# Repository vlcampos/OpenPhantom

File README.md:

# OpenPhantom
OpenPhantom is an open-source hardware project of a replacement main board for the Gradiente Phantom System model PH-8. The most famous NES clone made in Brazil during the 1980s and early 1990s.
The board was made as a hobby project based on a real board, internet schematics and a lot of reverse engineering.

Some modifications were made to make it easier to reproduce in Brazil and make it a little bit cheaper.
You can check the development progress on my twitter: @vagnerlc.
You are also invited to show any enhancements, modifications and make questions if needed.

You are free to use it in anyway you want: reproduce, sell, mod, etc.

I'm just a hobbyst trying to repair my old consoles and keep the very interesting history of this console alive.

The software used for the schematics was the Kicad 6.0.

Enjoy!

OpenPhantom é um projeto open-source para uma placa de reposição para o Phantom System PH-8 da Gradiente, o mais famoso dos clones de Nintendinho feitos no Brasil nas décadas de 80 e 90.
Essa placa surgiu como um hobby que envolveu uma placa com problemas, esquemas de internet e um bocado de engenharia revera.

Algumas modificações foram feitas para facilitar a reprodução da placa no Brasil.
Se quiserem acompanhar como foi o desenvolvimento é só ver meu twitter @vagnerlc.
Mandem as modificações, melhorias e projetos pessoais lá também e em caso de dúvidas é só me chamar por lá.

Por ser open source vocês podem usar o projeto do jeito que quiserem: venda, reprodução, modificação, etc...

Eu sou só um hobista tentando consertar minhas velharias e manter a história desse console viva.

Para o desenvolvimento foi utilizado o Kicad 6.0.

Divirtam-se!

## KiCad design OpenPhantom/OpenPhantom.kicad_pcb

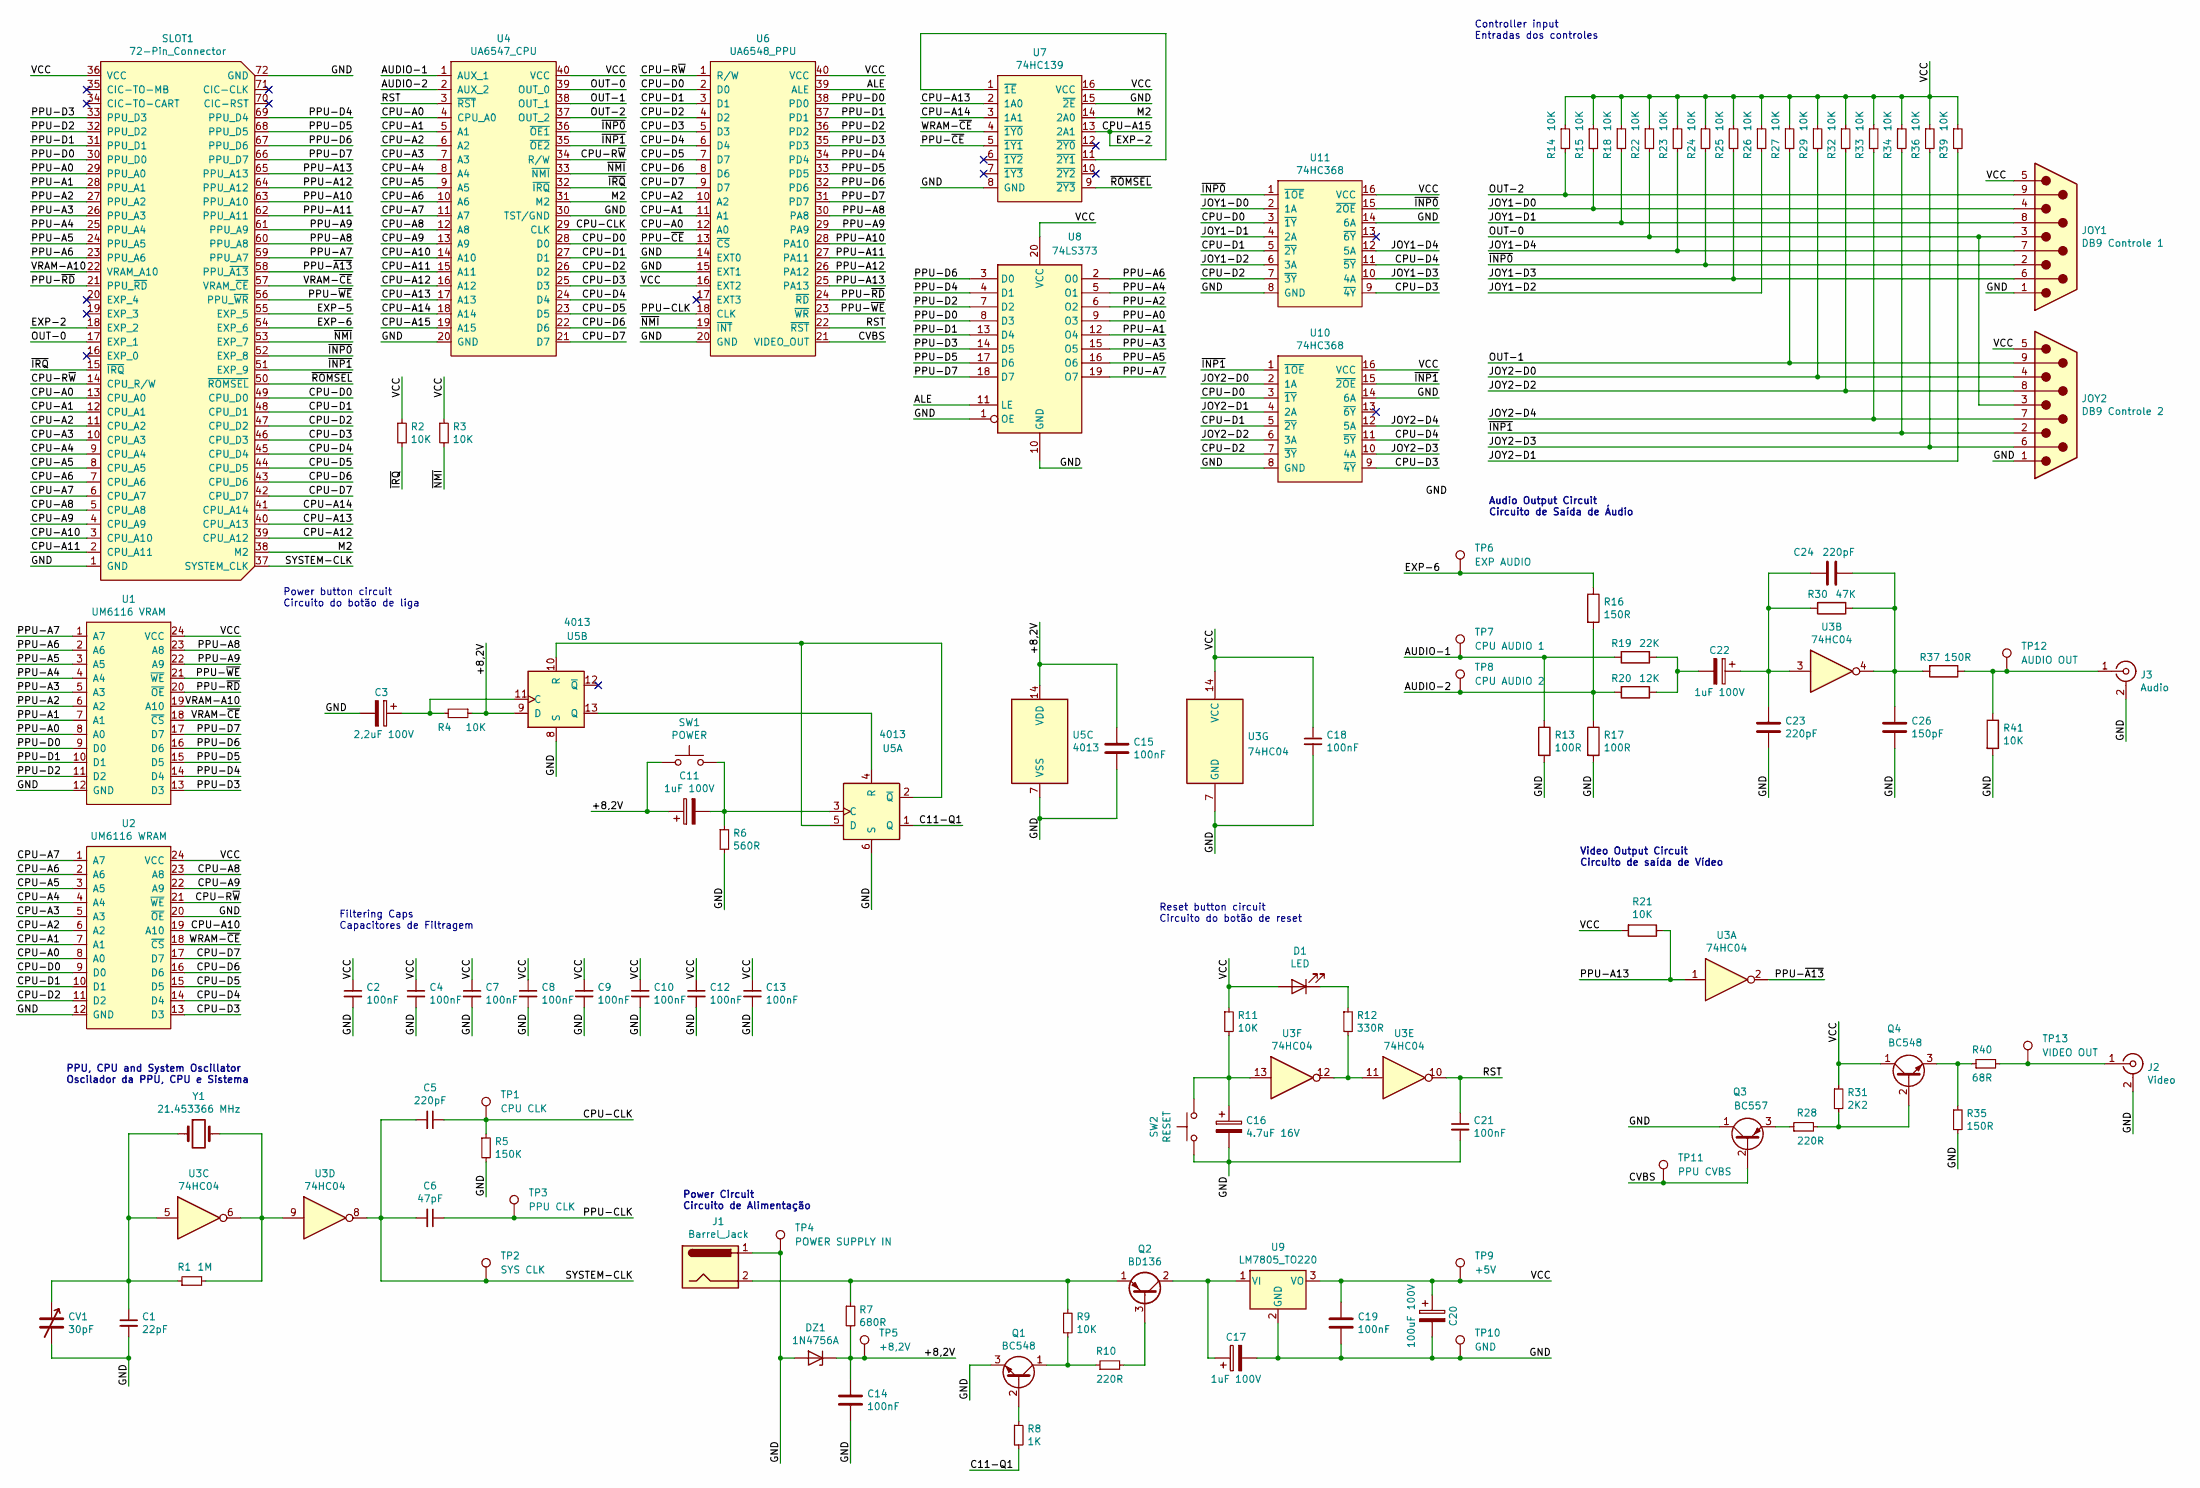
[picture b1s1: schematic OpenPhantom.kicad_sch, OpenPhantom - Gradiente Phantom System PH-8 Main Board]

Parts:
C1: 22pF; C_Disc_D4.7mm_W2.5mm_P5.00mm
C2, C4, C7, C8, C9, C10, C12, C13, C14, C15, C18, C19, C21: 100nF; C_Disc_D4.7mm_W2.5mm_P5.00mm
C3: 2,2uF 100V; CP_Radial_D5.0mm_P2.50mm
C5, C23, C24: 220pF; C_Disc_D4.7mm_W2.5mm_P5.00mm
C6: 47pF; C_Disc_D4.7mm_W2.5mm_P5.00mm
C11, C17, C22: 1uF 100V; CP_Radial_D5.0mm_P2.50mm
C16: 4.7uF 16V; CP_Radial_D5.0mm_P2.50mm
C20: 100uF 100V; CP_Radial_D5.0mm_P2.50mm
C26: 150pF; C_Disc_D4.7mm_W2.5mm_P5.00mm
CV1: 30pF; TrimmerCap-THT
D1: LED; LED_D5.0mm
DZ1: 1N4756A; D_DO-41_SOD81_P10.16mm_Horizontal
J1: Barrel_Jack; BarrelJack_Horizontal
J2: Video; rca_yellow
J3: Audio; rca_white
JOY1: DB9 Controle 1; DSUB-9_Male_Horizontal_P2.77x2.84mm_EdgePinOffset7.70mm_Hou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
JOY2: DB9 Controle 2; DSUB-9_Male_Horizontal_P2.77x2.84mm_EdgePinOffset7.70mm_Hou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
Q1, Q4: BC548; TO-92_HandSolder
Q2: BD136; TO-126-3_Vertical
Q3: BC557; TO-92_HandSolder
R1: 1M; R_Axial_DIN0207_L6.3mm_D2.5mm_P10.16mm_Horizontal
R2, R3, R4, R9, R11, R14, R15, R18, R21, R22, R23, R24, R25, R26, R27, R29, R32, R33, R34, R36, R39, R41: 10K; R_Axial_DIN0207_L6.3mm_D2.5mm_P10.16mm_Horizontal
R5: 150K; R_Axial_DIN0207_L6.3mm_D2.5mm_P10.16mm_Horizontal
R6: 560R; R_Axial_DIN0207_L6.3mm_D2.5mm_P10.16mm_Horizontal
R7: 680R; R_Axial_DIN0207_L6.3mm_D2.5mm_P10.16mm_Horizontal
R8: 1K; R_Axial_DIN0207_L6.3mm_D2.5mm_P10.16mm_Horizontal
R10: 220R; R_Axial_DIN0204_L3.6mm_D1.6mm_P7.62mm_Horizontal
R12: 330R; R_Axial_DIN0207_L6.3mm_D2.5mm_P10.16mm_Horizontal
R13, R17: 100R; R_Axial_DIN0207_L6.3mm_D2.5mm_P10.16mm_Horizontal
R16, R35, R37: 150R; R_Axial_DIN0207_L6.3mm_D2.5mm_P10.16mm_Horizontal
R19: 22K; R_Axial_DIN0207_L6.3mm_D2.5mm_P10.16mm_Horizontal
R20: 12K; R_Axial_DIN0207_L6.3mm_D2.5mm_P10.16mm_Horizontal
R28: 220R; R_Axial_DIN0207_L6.3mm_D2.5mm_P10.16mm_Horizontal
R30: 47K; R_Axial_DIN0207_L6.3mm_D2.5mm_P10.16mm_Horizontal
R31: 2K2; R_Axial_DIN0207_L6.3mm_D2.5mm_P10.16mm_Horizontal
R40: 68R; R_Axial_DIN0207_L6.3mm_D2.5mm_P10.16mm_Horizontal
SLOT1: 72-Pin_Connector; Conector_NES_72pinos
SW1: POWER; SW_PUSH_6mm
SW2: RESET; SW_PUSH_6mm
TP1: CPU CLK; TestPoint_Pad_1.0x1.0mm
TP2: SYS CLK; TestPoint_Pad_1.0x1.0mm
TP3: PPU CLK; TestPoint_Pad_1.0x1.0mm
TP4: POWER SUPPLY IN; TestPoint_Pad_1.0x1.0mm
TP5: +8,2V; TestPoint_Pad_1.0x1.0mm
TP6: EXP AUDIO; TestPoint_Pad_1.0x1.0mm
TP7: CPU AUDIO 1; TestPoint_Pad_1.0x1.0mm
TP8: CPU AUDIO 2; TestPoint_Pad_1.0x1.0mm
TP9: +5V; TestPoint_Pad_1.0x1.0mm
TP10: GND; TestPoint_Pad_1.0x1.0mm
TP11: PPU CVBS; TestPoint_Pad_1.0x1.0mm
TP12: AUDIO OUT; TestPoint_Pad_1.0x1.0mm
TP13: VIDEO OUT; TestPoint_Pad_1.0x1.0mm
U1: UM6116 VRAM; DIP-24_W15.24mm
U2: UM6116 WRAM; DIP-24_W15.24mm
U3: 74HC04; DIP-14_W7.62mm
U4: UA6547_CPU; DIP-40_W15.24mm
U5: 4013; DIP-14_W7.62mm
U6: UA6548_PPU; DIP-40_W15.24mm
U7: 74HC139; DIP-16_W7.62mm
U8: 74LS373; DIP-20_W7.62mm
U9: LM7805_TO220; TO-220-3_Vertical
U10, U11: 74HC368; DIP-16_W7.62mm
Y1: 21.453366 MHz; Crystal_HC18-U_Vertical

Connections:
/+8,2V: C11.1, C14.1, C15.1, DZ1.1 (K), R4.1, R7.2, SW1.1, TP5.1, U5.9 (D), U5.14 (VDD)
/ALE: U6.39 (ALE), U8.11 (LE)
/AUDIO-1: R13.1, R19.2, TP7.1, U4.1 (AUX_1)
/AUDIO-2: R16.2, R17.1, R20.2, TP8.1, U4.2 (AUX_2)
/C11-Q1: R8.2, U5.1 (Q)
/CPU-A0: SLOT1.13 (CPU_A0), U2.8 (A0), U4.4 (CPU_A0), U6.12 (A0)
/CPU-A1: SLOT1.12 (CPU_A1), U2.7 (A1), U4.5 (A1), U6.11 (A1)
/CPU-A2: SLOT1.11 (CPU_A2), U2.6 (A2), U4.6 (A2), U6.10 (A2)
/CPU-A3: SLOT1.10 (CPU_A3), U2.5 (A3~), U4.7 (A3)
/CPU-A4: SLOT1.9 (CPU_A4), U2.4 (A4~), U4.8 (A4)
/CPU-A5: SLOT1.8 (CPU_A5), U2.3 (A5~), U4.9 (A5)
/CPU-A6: SLOT1.7 (CPU_A6), U2.2 (A6~), U4.10 (A6)
/CPU-A7: SLOT1.6 (CPU_A7), U2.1 (A7), U4.11 (A7)
/CPU-A8: SLOT1.5 (CPU_A8), U2.23 (A8), U4.12 (A8)
/CPU-A9: SLOT1.4 (CPU_A9), U2.22 (A9), U4.13 (A9)
/CPU-A10: SLOT1.3 (CPU_A10), U2.19 (A10), U4.14 (A10)
/CPU-A11: SLOT1.2 (CPU_A11), U4.15 (A11)
/CPU-A12: SLOT1.39 (CPU_A12), U4.16 (A12)
/CPU-A13: SLOT1.40 (CPU_A13), U4.17 (A13), U7.2 (1A0)
/CPU-A14: SLOT1.41 (CPU_A14), U4.18 (A14), U7.3 (1A1)
/CPU-A15: SLOT1.18 (EXP_2), U4.19 (A15), U7.13 (2A1)
/CPU-CLK: C5.1, R5.1, TP1.1, U4.29 (CLK)
/CPU-D0: SLOT1.49 (CPU_D0), U2.9 (D0), U4.28 (D0), U6.2 (D0), U10.3 (~1Y), U11.3 (~1Y)
/CPU-D1: SLOT1.48 (CPU_D1), U2.10 (D1), U4.27 (D1), U6.3 (D1), U10.5 (~2Y), U11.5 (~2Y)
/CPU-D2: SLOT1.47 (CPU_D2), U2.11 (D2), U4.26 (D2), U6.4 (D2), U10.7 (~3Y), U11.7 (~3Y)
/CPU-D3: SLOT1.46 (CPU_D3), U2.13 (D3), U4.25 (D3), U6.5 (D3), U10.9 (~4Y), U11.9 (~4Y)
/CPU-D4: SLOT1.45 (CPU_D4), U2.14 (D4), U4.24 (D4), U6.6 (D4), U10.11 (~5Y), U11.11 (~5Y)
/CPU-D5: SLOT1.44 (CPU_D5), U2.15 (D5), U4.23 (D5), U6.7 (D7)
/CPU-D6: SLOT1.43 (CPU_D6), U2.16 (D6), U4.22 (D6), U6.8 (D6)
/CPU-D7: SLOT1.42 (CPU_D7), U2.17 (D7), U4.21 (D7), U6.9 (D7)
/CPU-R~W: SLOT1.14 (CPU_R/W), U2.21 (~WE), U4.34 (R/W), U6.1 (R/W)
/CVBS: Q3.2 (B), TP11.1, U6.21 (VIDEO_OUT)
/EXP-5: SLOT1.55 (EXP_5)
/EXP-6: R16.1, SLOT1.54 (EXP_6), TP6.1
/GND: C1.2, C2.2, C3.2, C4.2, C7.2, C8.2, C9.2, C10.2, C12.2, C13.2, C14.2, C15.2, C16.2, C17.2, C18.2, C19.2, C20.2, C21.2, C23.2, C26.2, CV1.2, DZ1.2 (A), J1.1, J2.2 (Ext), J3.2 (Ext), JOY1.1, JOY2.1, Q1.3 (E), Q3.1 (C), R5.2, R6.2, R13.2, R17.2, R35.2, R41.2, SLOT1.1 (GND), SLOT1.72 (GND), SW2.1, TP4.1, TP10.1, U1.12 (GND~), U2.12 (GND~), U2.20 (~OE), U3.7 (GND), U4.20 (GND), U4.30 (TST/GND), U5.6 (S), U5.7 (VSS), U5.8 (S), U6.14 (EXT0), U6.15 (EXT1), U6.20 (GND), U7.8 (GND), U7.15 (~2E), U8.1 (OE), U8.10 (GND), U9.2 (GND), U10.8 (GND), U10.14 (6A), U11.8 (GND), U11.14 (6A)
/JOY1-D0: JOY1.4, R15.2, U11.2 (1A)
/JOY1-D1: JOY1.8, R18.2, U11.4 (2A)
/JOY1-D2: R26.2, U11.6 (3A)
/JOY1-D3: JOY1.6, R25.2, U11.10 (4A)
/JOY1-D4: JOY1.7, R23.2, U11.12 (5A)
/JOY2-D0: JOY2.4, R29.2, U10.2 (1A)
/JOY2-D1: R39.2, U10.4 (2A)
/JOY2-D2: JOY2.8, R32.2, U10.6 (3A)
/JOY2-D3: JOY2.6, R36.2, U10.10 (4A)
/JOY2-D4: JOY2.7, R33.2, U10.12 (5A)
/M2: SLOT1.38 (M2), U4.31 (M2), U7.14 (2A0)
/OUT-0: JOY1.3, JOY2.3, R22.2, SLOT1.17 (EXP_1), U4.39 (OUT_0)
/OUT-1: JOY2.9, R27.2, U4.38 (OUT_1)
/OUT-2: JOY1.9, R14.2, U4.37 (OUT_2)
/PPU-A0: SLOT1.29 (PPU_A0), U1.8 (A0), U8.9 (O3)
/PPU-A1: SLOT1.28 (PPU_A1), U1.7 (A1), U8.12 (O4)
/PPU-A2: SLOT1.27 (PPU_A2), U1.6 (A2), U8.6 (O2)
/PPU-A3: SLOT1.26 (PPU_A3), U1.5 (A3~), U8.15 (O5)
/PPU-A4: SLOT1.25 (PPU_A4), U1.4 (A4~), U8.5 (O1)
/PPU-A5: SLOT1.24 (PPU_A5), U1.3 (A5~), U8.16 (O6)
/PPU-A6: SLOT1.23 (PPU_A6), U1.2 (A6~), U8.2 (O0)
/PPU-A7: SLOT1.59 (PPU_A7), U1.1 (A7), U8.19 (O7)
/PPU-A8: SLOT1.60 (PPU_A8), U1.23 (A8), U6.30 (PA8)
/PPU-A9: SLOT1.61 (PPU_A9), U1.22 (A9), U6.29 (PA9)
/PPU-A10: SLOT1.63 (PPU_A10), U6.28 (PA10)
/PPU-A11: SLOT1.62 (PPU_A11), U6.27 (PA11)
/PPU-A12: SLOT1.64 (PPU_A12), U6.26 (PA12)
/PPU-A13: R21.1, SLOT1.65 (PPU_A13), U3.1, U6.25 (PA13)
/PPU-CLK: C6.1, TP3.1, U6.18 (CLK)
/PPU-D0: SLOT1.30 (PPU_D0), U1.9 (D0), U6.38 (PD0), U8.8 (D3)
/PPU-D1: SLOT1.31 (PPU_D1), U1.10 (D1), U6.37 (PD1), U8.13 (D4)
/PPU-D2: SLOT1.32 (PPU_D2), U1.11 (D2), U6.36 (PD2), U8.7 (D2)
/PPU-D3: SLOT1.33 (PPU_D3), U1.13 (D3), U6.35 (PD3), U8.14 (D5)
/PPU-D4: SLOT1.69 (PPU_D4), U1.14 (D4), U6.34 (PD4), U8.4 (D1)
/PPU-D5: SLOT1.68 (PPU_D5), U1.15 (D5), U6.33 (PD5), U8.17 (D6)
/PPU-D6: SLOT1.67 (PPU_D6), U1.16 (D6), U6.32 (PD6), U8.3 (D0)
/PPU-D7: SLOT1.66 (PPU_D7), U1.17 (D7), U6.31 (PD7), U8.18 (D7)
/PPU-~A13: SLOT1.58 (PPU_~A13), U3.2
/PPU-~CE: U6.13 (~CS), U7.5 (~1Y1)
/PPU-~RD: SLOT1.21 (PPU_~RD), U1.20 (~OE), U6.24 (~RD)
/PPU-~WE: SLOT1.56 (PPU_~WR), U1.21 (~WE), U6.23 (~WR)
/RST: C21.1, U3.10, U4.3 (~RST), U6.22 (~RST)
/SYSTEM-CLK: C5.2, C6.2, SLOT1.37 (SYSTEM_CLK), TP2.1, U3.8
/VCC: C2.1, C4.1, C7.1, C8.1, C9.1, C10.1, C12.1, C13.1, C18.1, C19.1, C20.1, D1.2 (A), JOY1.5, JOY2.5, Q4.1 (C), R2.1, R3.1, R11.1, R14.1, R15.1, R18.1, R21.2, R22.1, R23.1, R24.1, R25.1, R26.1, R27.1, R29.1, R31.1, R32.1, R33.1, R34.1, R36.1, R39.1, SLOT1.36 (VCC), TP9.1, U1.24 (VCC), U2.24 (VCC), U3.14 (VCC), U4.40 (VCC), U6.16 (EXT2), U6.40 (VCC), U7.16 (VCC), U8.20 (VCC), U9.3 (VO), U10.16 (VCC), U11.16 (VCC)
/VRAM-A10: SLOT1.22 (VRAM_A10), U1.19 (A10)
/VRAM-~CE: SLOT1.57 (VRAM_~CE), U1.18 (~CS)
/WRAM-~CE: U2.18 (~CS), U7.4 (~1Y0)
/~INP0: JOY1.2, R24.2, SLOT1.52 (EXP_8), U4.36 (~OE1), U11.1 (~1OE), U11.15 (~2OE)
/~INP1: JOY2.2, R34.2, SLOT1.51 (EXP_9), U4.35 (~OE2), U10.1 (~1OE), U10.15 (~2OE)
/~IRQ: R2.2, SLOT1.15 (~IRQ), U4.32 (~IRQ)
/~NMI: R3.2, SLOT1.53 (EXP_7), U4.33 (~NMI), U6.19 (~INT)
/~ROMSEL: SLOT1.50 (~ROMSEL), U7.9 (~2Y3)
unnamed: C1.1, CV1.1, R1.1, U3.5, Y1.1
unnamed: C3.1, R4.2, U5.11 (C)
unnamed: C11.2, R6.1, SW1.2, U5.3 (C)
unnamed: C16.1, R11.2, SW2.2, U3.13
unnamed: C17.1, Q2.2 (C), U9.1 (VI)
unnamed: C22.1, C23.1, C24.2, R30.2, U3.3
unnamed: C22.2, R19.1, R20.1
unnamed: C24.1, C26.1, R30.1, R37.2, U3.4
unnamed: D1.1 (K), R12.1
unnamed: J1.2, Q2.1 (E), R7.1, R9.1
unnamed: J2.1 (In), R40.2, TP13.1
unnamed: J3.1 (In), R37.1, R41.1, TP12.1
unnamed: Q1.1 (C), R9.2, R10.1
unnamed: Q1.2 (B), R8.1
unnamed: Q2.3 (B), R10.2
unnamed: Q3.3 (E), R28.1
unnamed: Q4.2 (B), R28.2, R31.2
unnamed: Q4.3 (E), R35.1, R40.1
unnamed: R1.2, U3.6, U3.9, Y1.2
unnamed: R12.2, U3.11, U3.12
unnamed: U5.2 (~Q), U5.5 (D), U5.10 (R)
unnamed: U5.4 (R), U5.13 (Q)
unnamed: U7.1 (~1E), U7.11 (~2Y1)

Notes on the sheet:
PPU, CPU and System Oscillator Oscilador da PPU, CPU e Sistema
Audio Output Circuit Circuito de Saída de Áudio
Controller input Entradas dos controles
Power button circuit Circuito do botão de liga
Power Circuit Circuito de Alimentação
Video Output Circuit Circuito de saída de Vídeo
Reset button circuit Circuito do botão de reset
Filtering Caps Capacitores de Filtragem

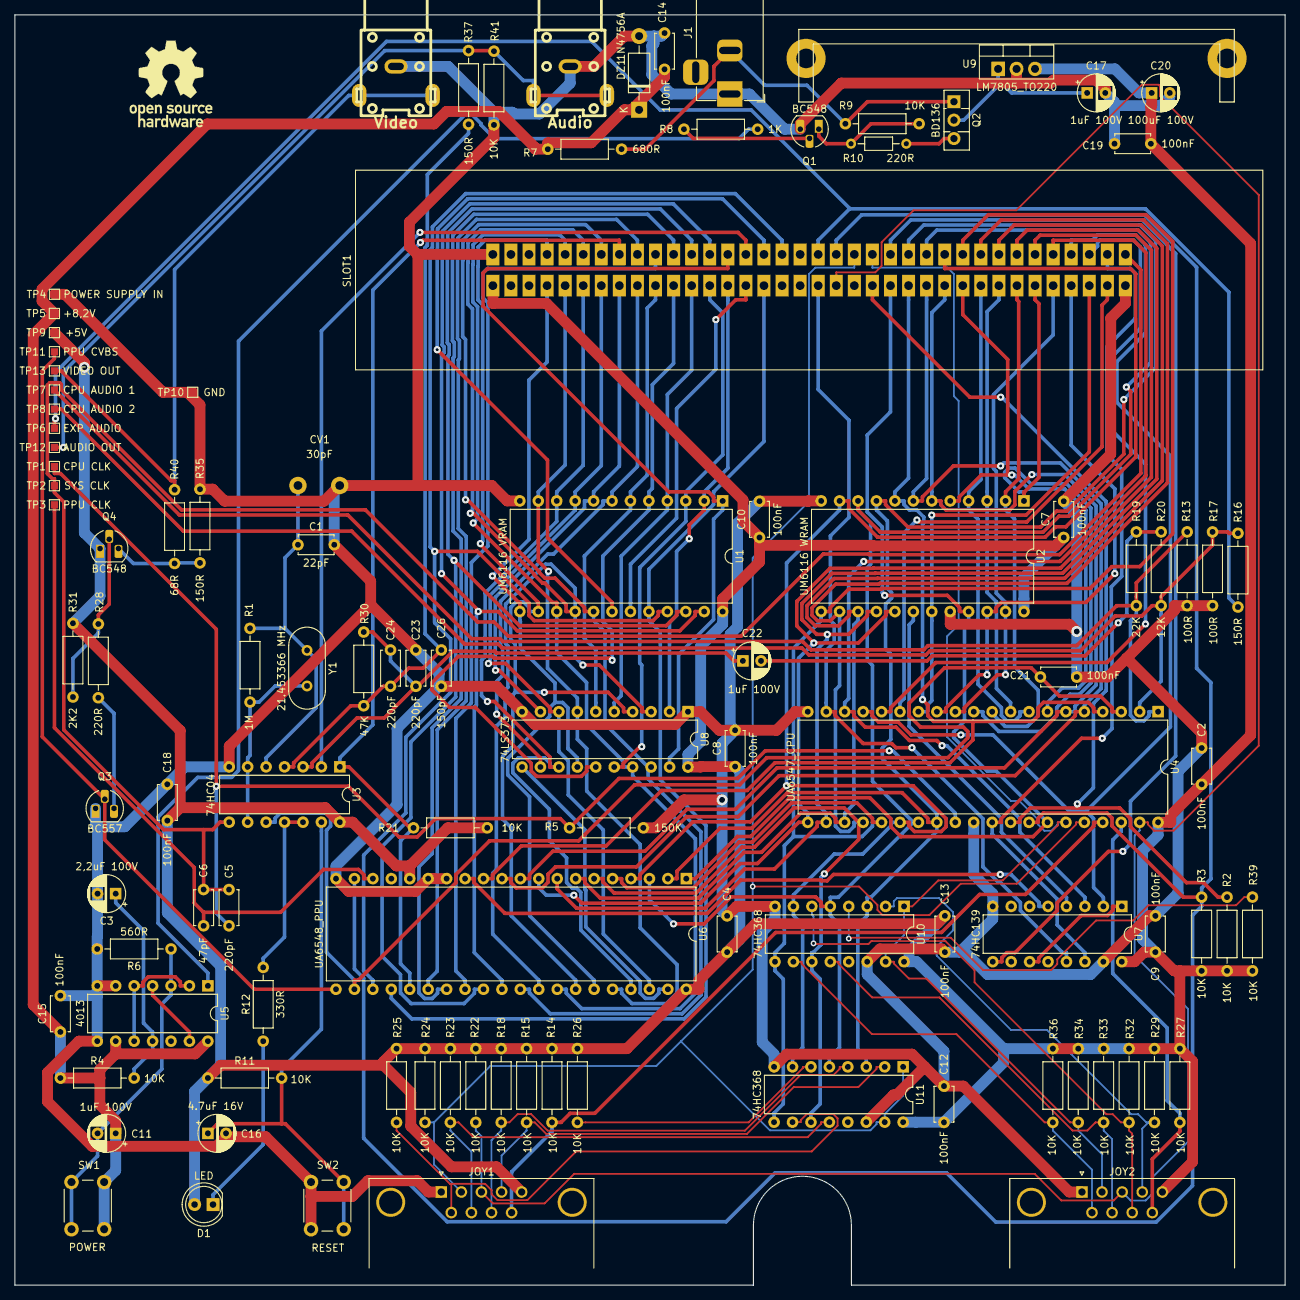
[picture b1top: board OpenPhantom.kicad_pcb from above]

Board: 2 copper layers, 175.0 x 175.0 mm, 107 parts (0 on the bottom side), 109 nets.

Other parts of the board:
PT1, PT2: MountingHole_2.7mm_M2.5_Pad

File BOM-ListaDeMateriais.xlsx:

Bill of Materials/Lista de Materiais OpenPhantom
Referência/Reference | QTD/QTY | Descrição/Description
C1 | 1 | Capacitor Cerâmico/Ceramic Capacitor 22pF
C2, C4, C7, C8, C9, C10, C12, C13, C14, C15, C18, C19, C21 | 13 | Capacitor Cerâmico/Ceramic Capacitor 100nF
C3 | 1 | Capacitor Cerâmico/Ceramic Capacitor 2,2uF 100V
C5, C23, C24 | 3 | Capacitor Cerâmico/Ceramic Capacitor 220pF
C6 | 1 | Capacitor Cerâmico/Ceramic Capacitor 47pF
C11, C17, C22 | 3 | Capacitor Eletrolítico/Electrolytic Capacitor 1uF 100V
C16 | 1 | Capacitor Eletrolítico/Electrolytic Capacitor 4.7uF 16V
C20 | 1 | Capacitor Eletrolítico/Electrolytic Capacitor 100uF 100V
C25 | 1 | Capacitor Eletrolítico/Electrolytic Capacitor 22uF 25V
CV1 | 1 | Capacitor Trimmer (Variável)/Trimmer Cap 30pF
D1 | 1 | LED Vermelho/Red LED
DZ1 | 1 | Diodo Zenner/Zenner Diode 8V2 1W
J1 | 1 | Conector Jack P4 Fêmea
J2 | 1 | Tomada RCA Amarelo/Yellow RCA Jack
J3 | 1 | Tomada RCA Branca/White RCA Jack
JOY1 | 1 | Conector Curto DB9 Macho/Short DB9 Male Connector
JOY2 | 1 | Conector Curto DB9 Macho/Short DB9 Male Connector
Q1 | 2 | Transistor NPN BC548
Q2 | 1 | Transistor BD136
Q3 | 1 | Transistor PNP BC557
R1 | 1 | Resistor 1/4W 1M ohm
R2, R3, R4, R9, R11, R14, R15, R18, R21, R22, R23, R24, R25, R26, R27, R29, R32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 | 22 | Resistor 1/4W 10K ohm
R5 | 1 | Resistor 1/4W 150K
R6 | 1 | Resistor 1/4W 560R
R7 | 1 | Resistor 1/4W 680R
R8, R42 | 2 | Resistor 1/4W 1K ohm
R10 | 1 | Resistor 1/4W 220R
R12 | 1 | Resistor 1/4W 330R
R13, R17 | 2 | Resistor 1/4W 100R
R16, R37, R38 | 3 | Resistor 1/4W 150R
R19 | 1 | Resistor 1/4W 22K
R20 | 1 | Resistor 1/4W 12K
R28, R35 | 2 | Resistor 1/4W 220R
R30 | 1 | Resistor 1/4W 47K
R31 | 1 | Resistor 1/4W 2K2
R40 | 1 | Resistor 1/4W 68R
SLOT1 | 1 | Conector 72 Pinos para NES/72 Pin Connector
SW1 | 1 | Chave táctil 6mm/6mm Tactile Switch
SW2 | 1 | Chave táctil 6mm/6mm Tactile Switch
U1 | 1 | CI HM6116 ou UM6116
U2 | 1 | CI HM6116 ou UM6116
U3 | 1 | 74HC04
U4 | 1 | UMC UA6547 CPU
U5 | 1 | CD4013
U6 | 1 | UMC UA6548 PPU
U7 | 1 | 74HC139
U8 | 1 | 74LS373
U9 | 1 | LM7805
U10, U11 | 2 | 74HC368
Y1 | 1 | Cristal/Crystal Oscillator 21.453366 MHz

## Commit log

2022-04-19 Board files
    First upload
2022-04-20 PDF + PCB Routing + `Placement
    Corrected component position. Added PCB Schematic PDF. Changed the logo. Moved the RCA connectors 2mm closer to the PCB edge.
2022-04-30 New BOM + Schematic
    Updated Bill of Materials and Schematics
2022-05-01 BOM Update
2022-05-26 Updated track and vias width
    After some comments of other people that used the board, I remade the routing using a wider ground track. The other tracks were made wider too.
2022-06-22 74LS373 PPU AD Pins FIX
    Fixed 74LS373 pins connected to the AD Pins from PPU (PPU D0 to D7)
2022-08-01 Fixed Routes
    Power route fix.
2022-08-02 RCA Plug fix
    Fixed RCA plug pinout
2022-10-27 Added C26 + RF circuit removed
    Added C26 removed RF circuit components fixing audio noise.
2022-11-13 Added R35
    Added R35 to improved image quality.
2022-11-13 Fixed PDF Schematic
2022-12-12 Player controller fixed
2022-12-13 Joy port fix.
